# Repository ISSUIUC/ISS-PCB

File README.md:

# Welcome to the ISS-PCB repo! 🖥️⚙️⚡

# Repository Overview

* Boards: Contains all of the present boards the team is working on
    - Moved Board Archive to the [Archive](https://github.com/ISSUIUC/ISS-PCB-Archive) repo... check it out! 😁
* Docs: Contains various documents pertaining to PCB designs
* Libs: Contains various templates, symbols and footprints that we use when designing PCBs
* Scripts: Contains various codes used in PCB development
* Documentation & Tutorial Mark Down Files: 
    - README.md: Introduces the ISS-PCB Repo and pertinent information to become an amazing E-Hardware member
    - ISS-PCB-CONVENTIONS.md: Sets conventions to be followed when desiging for the ISS-PCB KiCad repo
    - HOW-TO.md: Presents brief and thorough lessons on important KiCad tools, documenation procedures, and design processes
    - GITHUB.md: An introduction to GitHub and how to use it for KiCad
    - CONTRIBUTING.md: Showcases how to setup KiCad and contribute proper work to E-Hardware. Additionally, introduces many conventions of ISS-PCB folder. 

When you commit changes to the repository, they will generally be found in the Boards folder. 

# E-Hardware PCB Documentation 

* You can find documentation about all of our PCBs in the [Spaceshot Members Box Folder](https://uofi.app.box.com/folder/273741222408). 
    - Alternatively, [Members] Spaceshot > Avionics > Development 

# How to contribute:
There are many ways to contribute to the PCBs that we build for the rocket and its accompanying systems. The timeline for building a PCB is usually as follows: 

* Formulate the requirements of the board
* Research different chips, understand their functionalities, and determine if we can use it for our purposes
* Build the board schematic using the datasheets of different chips 
* Route the board 
* Once the board is manufactured, solder all the components onto the board
* Debug the board 
* Document the board (this should be done throughout the process as well) 

Every part of constructing a PCB is hands-on, and there are lots of ways to get involved. 

To have your changes reflected on the board, it is important to commit your changes to the Github repository. To learn how to commit changes, check out the [Contributing Guide](/CONTRIBUTING.md).

# Useful Links:
Here are some links you may find useful as you are building PCBs: 

* [KiCad](https://www.kicad.org/) - software used for designing PCBs 

* [KiCad Library Conventions](https://klc.kicad.org/) - guidelines for creation of symbols, footprints, and 3D models in KiCad

* [DigiKey](https://www.digikey.com/) - used for looking up various electronic components

* [Mouser](https://www.mouser.com/) - used for looking up various electronic components

* [JLCPCB](https://jlcpcb.com) - the PCB manufacturer we primarily use

* [JLCPCB Design Rules](https://jlcpcb.com/capabilities/Capabilities) - the design constraints JLCPCB imposes

Thanks for reading, and good luck in building PCBs! 

*See a typo? Think we left some vital information out? Make a branch and edit this file!*

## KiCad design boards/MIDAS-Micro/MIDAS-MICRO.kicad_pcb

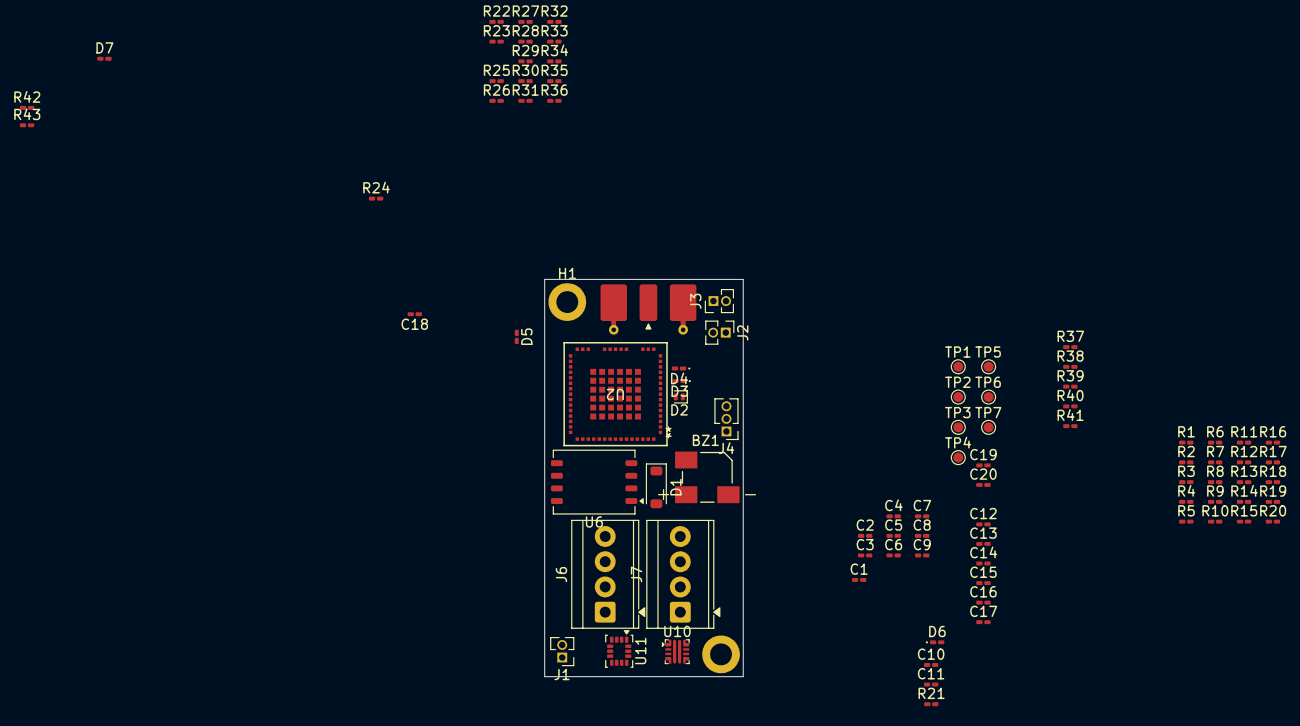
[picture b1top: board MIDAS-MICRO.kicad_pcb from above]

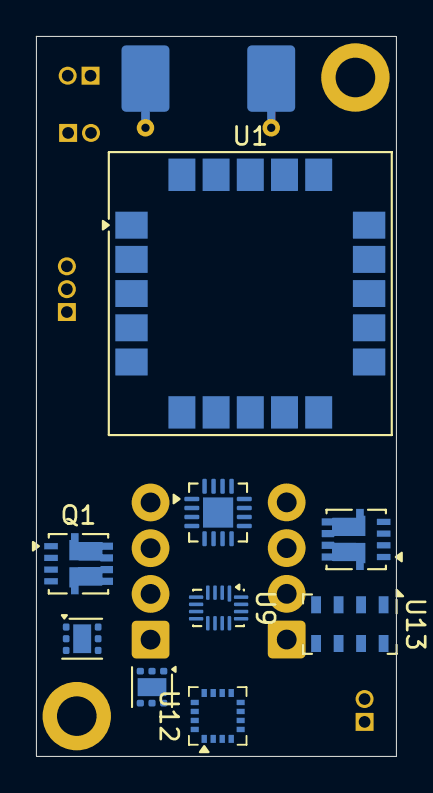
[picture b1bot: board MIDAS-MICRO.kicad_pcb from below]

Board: 2 copper layers, 20.0 x 40.0 mm, 100 parts (9 on the bottom side), 61 nets, no tracks yet.

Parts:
BZ1: Buzzer; XDCR_SMT-0540-T-9-R
C1, C2, C5, C6, C13, C15, C16, C17, C19, C20: 100nF; C_0201_0603Metric_Pad0.64x0.40mm_HandSolder
C3: 22uF; C_0201_0603Metric_Pad0.64x0.40mm_HandSolder
C4, C7, C8, C9, C10: 1uF; C_0201_0603Metric_Pad0.64x0.40mm_HandSolder
C11, C14: 4.7uF; C_0201_0603Metric_Pad0.64x0.40mm_HandSolder
C12: 4.7nF; C_0201_0603Metric_Pad0.64x0.40mm_HandSolder
C18: 10uF; C_0201_0603Metric_Pad0.64x0.40mm_HandSolder
D1: 1N4148W; D_SOD-123
D2: SDM05U40CSP; D_SOD-882
D3: RED LED; LED_0201_0603Metric_Pad0.64x0.40mm_HandSolder
D4: ORANGE LED; LED_0201_0603Metric_Pad0.64x0.40mm_HandSolder
D5: GREEN LED; L_0201_0603Metric_Pad0.64x0.40mm_HandSolder
D6: BLUE LED; LED_0201_0603Metric_Pad0.64x0.40mm_HandSolder
D7: RED LED; L_0201_0603Metric_Pad0.64x0.40mm_HandSolder
H1, H2: M2; MountingHole_2.2mm_M2_DIN965_Pad
J1, J2, J3: Conn_01x02; PinHeader_1x02_P1.27mm_Vertical
J4: Conn_01x03; PinHeader_1x03_P1.27mm_Vertical
J5: SMA; SMA_Molex_73251-2120_EdgeMount_Horizontal
J6, J7: Screw_Terminal_01x04; TerminalBlock_TE_282834-4_1x04_P2.54mm_Horizontal
Q1, Q2: Si7232DN; Vishay_PowerPAK_1212-8_Dual
R1, R25, R36, R40: 3.3k; R_0201_0603Metric_Pad0.64x0.40mm_HandSolder
R2, R29, R33, R37, R41: 1k; R_0201_0603Metric_Pad0.64x0.40mm_HandSolder
R3, R24, R28: 10k; R_0201_0603Metric_Pad0.64x0.40mm_HandSolder
R4: 560k; R_0201_0603Metric_Pad0.64x0.40mm_HandSolder
R5, R6, R7, R8, R9, R20, R27, R30, R35, R38, R42: 100k; R_0201_0603Metric_Pad0.64x0.40mm_HandSolder
R10, R11, R12, R13, R23: 470; R_0201_0603Metric_Pad0.64x0.40mm_HandSolder
R14, R15, R16, R18, R19: 50k; R_0201_0603Metric_Pad0.64x0.40mm_HandSolder
R17, R21: 4.7k; R_0201_0603Metric_Pad0.64x0.40mm_HandSolder
R22: 20k; R_0201_0603Metric_Pad0.64x0.40mm_HandSolder
R26, R34: 150k; R_0201_0603Metric_Pad0.64x0.40mm_HandSolder
R31, R39, R43: 18k; R_0201_0603Metric_Pad0.64x0.40mm_HandSolder
R32: 820; R_0201_0603Metric_Pad0.64x0.40mm_HandSolder
TP1, TP2, TP3, TP4, TP5, TP6, TP7: TestPoint_Small; TestPoint_Pad_D1.0mm
U1: SAM-M10Q; ublox_SAM-M8Q
U2: STM32WL5MOCH6STR; STM32WL5MOC
U5: ADS7138-Q1; WQFN-16-1EP_3x3mm_P0.5mm_EP1.68x1.68mm
U6: XTSD04G; LGA-8_8x6.2mm_P1.27mm
U7: TVS1800DRV; WSON-6-1EP_2x2mm_P0.65mm_EP1x1.6mm
U8: TPS746-Q1; WSON-6-1EP_2x2mm_P0.65mm_EP1x1.6mm
U9: TCAL9538; UQFN-16_1.8x2.6mm_P0.4mm
U10: TPS25947; VQFN-HR-RPW0010A
U11: LSM6DSV320X; LGA-14_3x2.5mm_P0.5mm_LayoutBorder3x4y
U12: MMC5983MA; LGA-16_3x3mm_P0.5mm
U13: MS5611-01BA; LGA-8_3x5mm_P1.25mm

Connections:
+3V3: C1.2, C2.2, C3.1, C5.1, C6.2, C7.1, C8.1, C11.1, C13.2, C15.1, C16.1, C17.1, C19.1, C20.1, D1.1 (K), J2.1, R14.2, R15.2, R16.2, R17.2, R18.2, R19.2, R21.2, R22.2, R23.1, R24.2, R28.2, R33.2, U1.2 (VCC_IO), U1.17 (VCC), U5.7 (AVDD), U5.10 (DVDD), U6.8 (VDD), U8.1 (OUT), U9.14 (VCC), U11.5 (VDDIO), U11.8 (VDD), U12.2 (VDD), U12.13 (VDDIO), U13.1 (VDD)
/ANT: J5.1 (In), U2.17 (ANT)
/BUZZER: R1.1, R2.1
/EXP_INT: R28.1, U9.11 (INT)
/EXP_RESET: R24.1, TP1.1 (1_1), U9.1 (~RESET)
/FLASH_CMD: R19.1, TP5.1 (1_1)
/FLASH_DAT0: R14.1, TP7.1 (1_1)
/I2C_SCL: R21.1, U1.12 (SCL), U2.42 (PA12), U5.13 (SCL), U9.12 (SCL)
/I2C_SDA: R17.1, U1.9 (SDA), U2.40 (PA11), U5.14 (SDA), U9.13 (SDA)
/JTCK/SWCLK: J4.2, U2.46 (PA14)
/JTDO: J4.3, U2.56 (PB3)
/JTMS/SWDIO: J4.1, U2.41 (PA13)
/LED_BLUE: R13.1, U2.6 (PA1)
/LED_GREEN: R12.1, U2.9 (PA2)
/LED_ORANGE: R11.1, U2.8 (PA3)
/LED_RED: R10.1, U2.12 (PA4)
/LSM_CS: TP4.1 (1_1), U2.31 (PA9), U11.12 (CS)
/MAG_CS: TP2.1 (1_1), U2.14 (PA8), U12.4 (CS)
/MS5611_CS: TP3.1 (1_1), U2.39 (PA10), U13.4 (CSB), U13.5 (CSB)
/NRST: C9.1, R22.1, U2.1 (NRST)
/PYRO_A: J6.2, Q2.6 (D1), R30.2
/PYRO_B: J6.4, Q2.5 (D2), R38.2
/PYRO_C: J7.3, Q1.5 (D2), R42.2
/PYRO_SENSE: R4.2, R5.1, U5.1 (ANI2/GPIO2)
/Pyro/FIRE_A: R25.1, R29.1, U9.2 (P0)
/Pyro/FIRE_B: R36.1, R37.1, U9.3 (P1)
/Pyro/FIRE_C: R40.1, R41.1, U9.10 (P7)
/Pyro/PGTH: R34.2, R35.1, U10.4 (PGTH/NFLT)
/Pyro/PYRO_EN: R26.2, R27.1, U9.5 (P3), U10.1 (EN/UVLO)
/Pyro/PYRO_PG: R33.1, U9.7 (P4), U10.3 (PG/AUXOFF)
/SENSE_A: R30.1, R31.2, U5.15 (AIN0/GPIO0)
/SENSE_B: R38.1, R39.2, U5.16 (AIN1/GPIO1)
/SENSE_C: R42.1, R43.2, U5.3 (AIN4/GPIO4)
/SPI_MISO: U2.50 (PA6), U11.1 (SDO/TA0), U12.5 (SDO), U13.6 (SDO)
/SPI_MOSI: U2.10 (PA7), U11.14 (SDA), U12.16 (SDI), U13.7 (SDI/SDA)
/SPI_SCK: U2.13 (PA5), U11.13 (SCL), U12.1 (SCK), U13.8 (SCLK)
/VBAT: C10.1, J7.2, U7.4 (IN), U7.5 (IN), U7.6 (IN), U8.4 (EN), U8.6 (IN)
/VBAT_PYRO: D2.2 (A), J1.1, R26.1, U10.5 (IN)
/VBAT_SENSE: R6.2, R7.1, U5.6 (AIN7/GPIO7)
/VCAP_SENSE: R8.2, R9.1, U5.5 (AIN6/GPIO6)
/V_PYRO: C14.1, J6.1, J6.3, J7.4, R34.1, U10.6 (OUT)
GND: C1.1, C2.1, C3.2, C4.2, C5.2, C6.1, C7.2, C8.2, C9.2, C10.2, C11.2, C12.2, C13.1, C14.2, C15.2, C16.2, C17.2, C18.2, C19.2, C20.2, D3.1 (K), D4.1 (K), D5.1 (K), D6.1 (K), D7.1 (K), J1.2, J2.2, J5.2 (Ext), J7.1, Q1.1 (S1), Q1.3 (S2), Q2.1 (S1), Q2.3 (S2), R1.2, R3.1, R5.2, R7.2, R9.2, R25.2, R27.2, R31.1, R32.2, R35.2, R36.2, R39.1, R40.2, R43.1, U1.1 (GND), U1.4 (GND), U1.5 (GND), U1.6 (GND), U1.10 (GND), U1.11 (GND), U1.15 (GND), U1.16 (GND), U1.20 (GND), U2.24 (BIAS_LP), U5.9 (GND), U5.17 (EPAD), U6.4 (VSS), U7.1 (GND), U7.2 (GND), U7.3 (GND), U7.7 (GND), U8.3 (GND), U8.7 (EP), U9.6 (GND), U9.15 (A0), U9.16 (A1), U10.8 (GND), U11.2 (SDx), U11.3 (SCx), U11.6 (GND), U11.7 (GND), U12.9 (GND), U12.11 (GND), U13.2 (PS), U13.3 (GND)
unnamed: D1.2 (A), Q1.6 (D1)
unnamed: D2.1 (K), R4.1
unnamed: D3.2 (A), R10.2
unnamed: D4.2 (A), R11.2
unnamed: D5.2 (A), R12.2
unnamed: D6.2 (A), R13.2
unnamed: D7.2 (A), R23.2
unnamed: Q1.2 (G1), R2.2
unnamed: Q1.4 (G2), R41.2
unnamed: Q2.2 (G1), R29.2
unnamed: Q2.4 (G2), R37.2
unnamed: R3.2, U2.15 (PH3-BOOT0)
unnamed: R20.1, U5.11 (ADDR)
unnamed: C4.1, R20.2, U5.8 (DECAP)
unnamed: R32.1, U10.9 (ILM)
unnamed: C12.1, U10.10 (ITIMER)
unnamed: C18.1, U12.10 (CAP)
VSS: U2.19 (VSS), U2.20 (VSS), U2.21 (VSS), U2.22 (VSS), U2.23 (VSS), U2.57 (VSS), U2.58 (VSS), U2.59 (VSS), U2.60 (VSS), U2.61 (VSS), U2.62 (VSS), U2.63 (VSS), U2.64 (VSS), U2.65 (VSS), U2.66 (VSS), U2.67 (VSS), U2.68 (VSS), U2.69 (VSS), U2.70 (VSS), U2.71 (VSS), U2.72 (VSS), U2.73 (VSS), U2.74 (VSS), U2.75 (VSS), U2.76 (VSS), U2.77 (VSS), U2.78 (VSS), U2.79 (VSS), U2.80 (VSS), U2.81 (VSS), U2.82 (VSS), U2.83 (VSS), U2.84 (VSS), U2.85 (VSS), U2.86 (VSS), U2.87 (VSS), U2.88 (VSS), U2.89 (VSS), U2.90 (VSS), U2.91 (VSS), U2.92 (VSS)
VSSRF: U2.16 (VSSRF), U2.18 (VSSRF)

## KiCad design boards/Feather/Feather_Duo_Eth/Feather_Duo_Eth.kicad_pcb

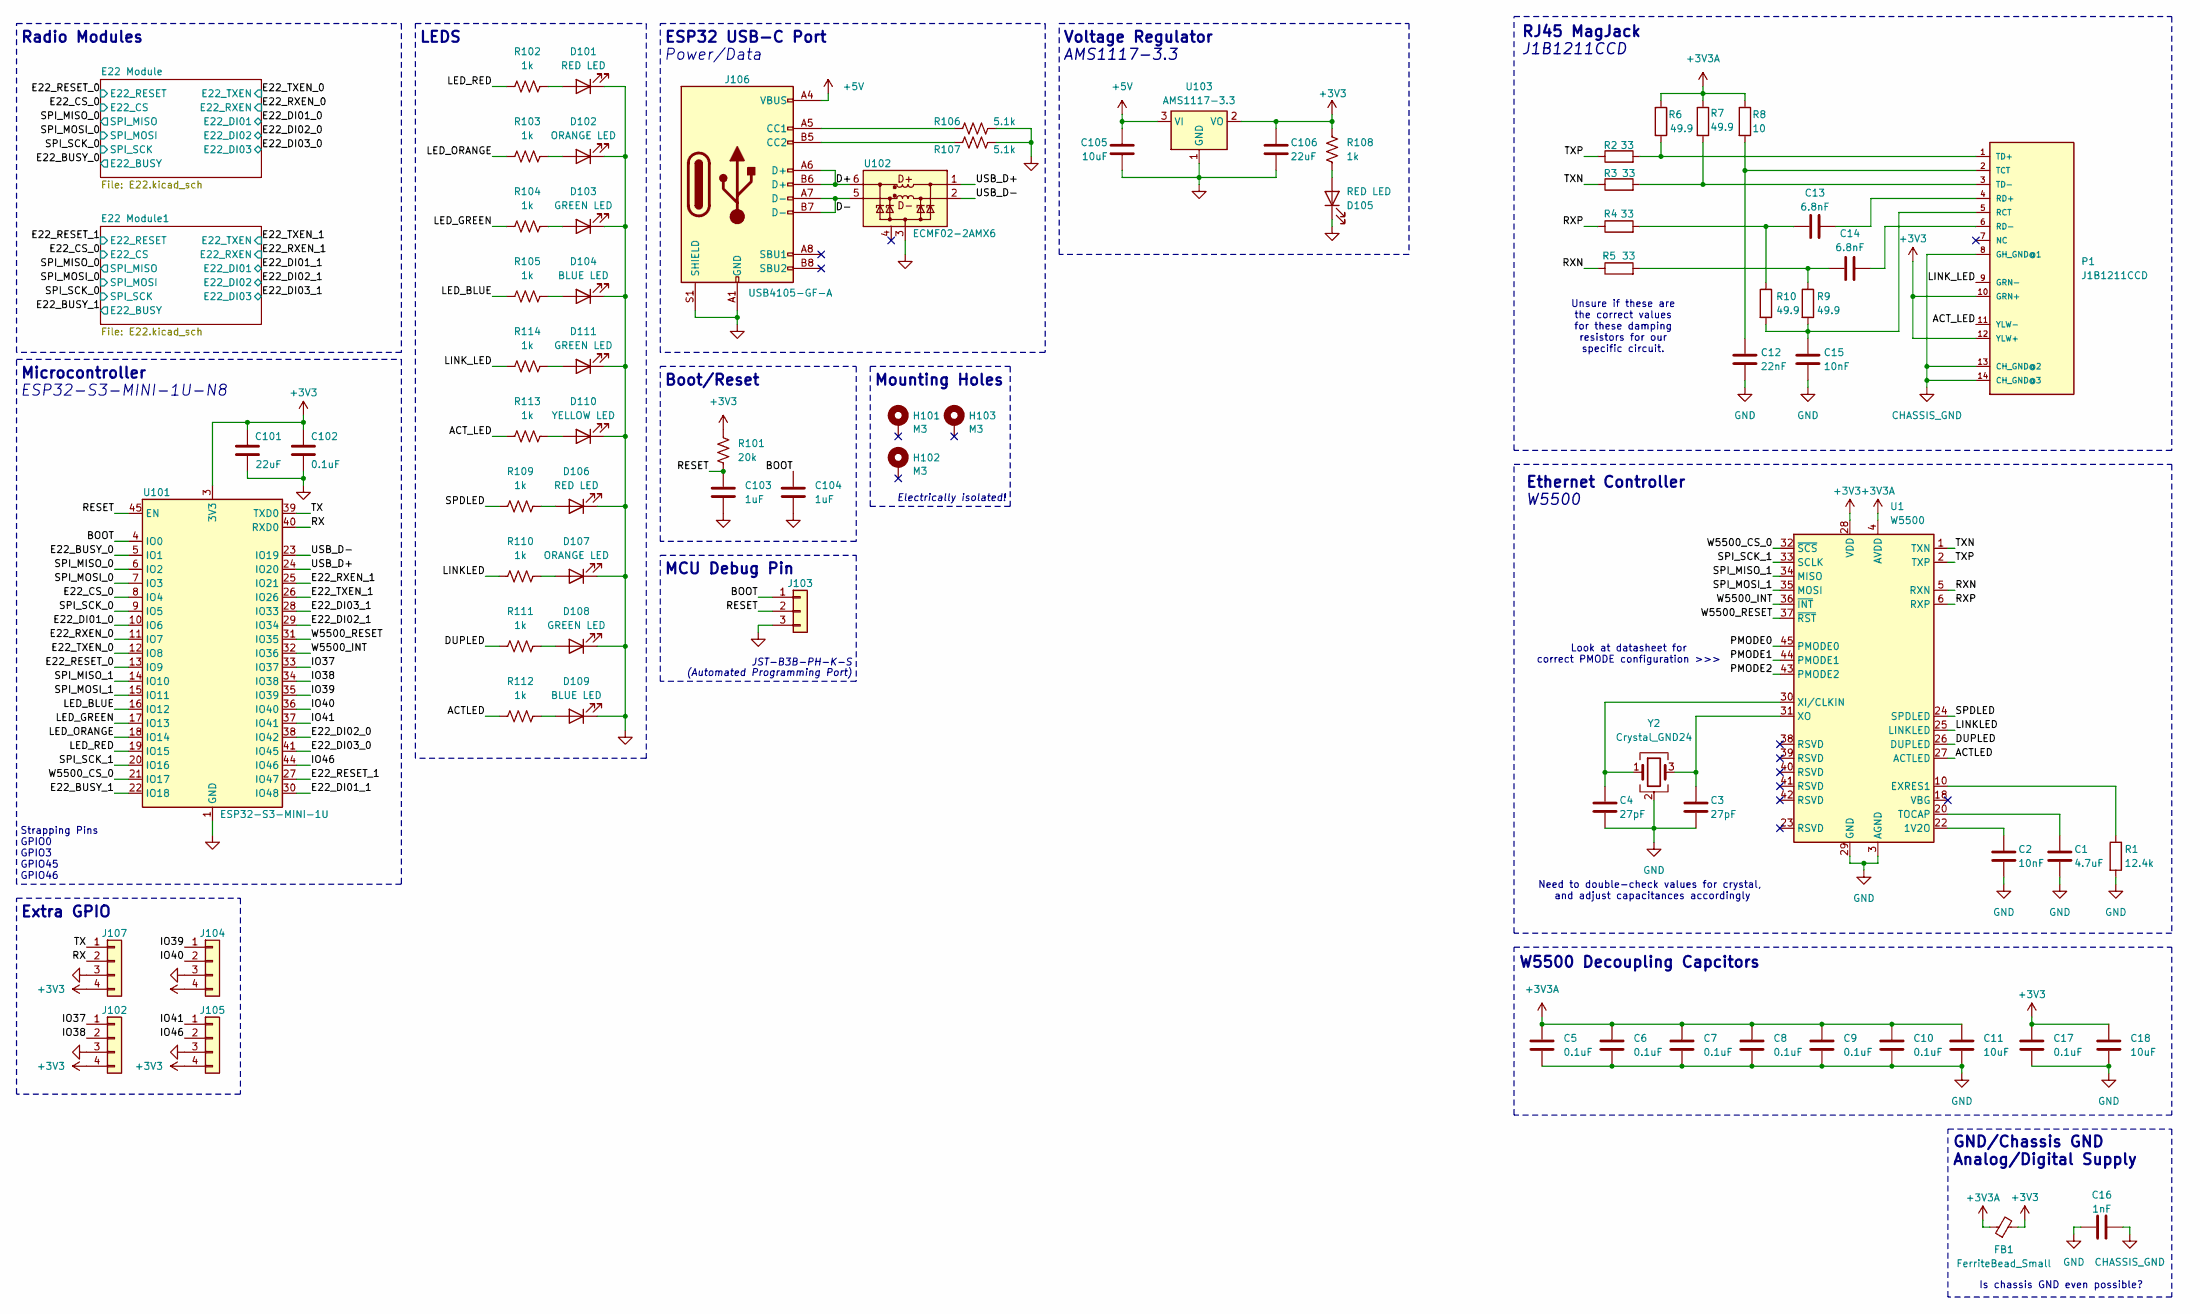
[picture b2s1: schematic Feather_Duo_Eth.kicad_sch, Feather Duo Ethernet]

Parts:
C1: 4.7uF; C_0603_1608Metric
C2, C15: 10nF; C_0603_1608Metric
C3, C4: 27pF; C_0603_1608Metric
C5, C6, C7, C8, C9, C10, C17, C102: 0.1uF; C_0603_1608Metric
C11, C18, C105: 10uF; C_0603_1608Metric
C12: 22nF; C_0603_1608Metric
C13, C14: 6.8nF; C_0603_1608Metric
C16: 1nF; C_0603_1608Metric
C101, C106: 22uF; C_0603_1608Metric
C103, C104: 1uF; C_0603_1608Metric
D101, D105, D106: RED LED; LED_0603_1608Metric
D102, D107: ORANGE LED; LED_0603_1608Metric
D103, D108, D111: GREEN LED; LED_0603_1608Metric
D104, D109: BLUE LED; LED_0603_1608Metric
D110: YELLOW LED; LED_0603_1608Metric
FB1: FerriteBead_Small; L_0805_2012Metric
H101, H102, H103: M3; MountingHole_3.2mm_M3_Pad_Via
J102, J104, J105, J107: Conn_01x04; PinHeader_1x04_P2.54mm_Vertical
J103: Conn_01x03; JST_PH_B3B-PH-K_1x03_P2.00mm_Vertical
J106: USB4105-GF-A; USB_C_Receptacle_GCT_USB4105-xx-A_16P_TopMnt_Horizontal
P1: J1B1211CCD
R1: 12.4k; R_0603_1608Metric
R2, R3, R4, R5: 33; R_0603_1608Metric
R6, R7, R9, R10: 49.9; R_0603_1608Metric
R8: 10; R_0603_1608Metric
R101: 20k; R_0603_1608Metric
R102, R103, R104, R105, R108, R109, R110, R111, R112, R113, R114: 1k; R_0603_1608Metric
R106, R107: 5.1k; R_0603_1608Metric
U1: W5500; LQFP-48_7x7mm_P0.5mm
U101: ESP32-S3-MINI-1U; ESP32-S2-MINI-1U
U102: ECMF02-2AMX6; ST_UQFN-6L_1.5x1.7mm_P0.5mm
U103: AMS1117-3.3; SOT-223-3_TabPin2
Y2: Crystal_GND24; Crystal_SMD_3225-4Pin_3.2x2.5mm

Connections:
+3V3: C17.1, C18.1, C101.2, C102.2, C106.1, FB1.2, J102.4, J104.4, J105.4, J107.4, P1.10 (GRN+), P1.12 (YLW+), R101.1, R108.1, U1.28 (VDD), U101.3 (3V3), U103.2 (VO); also elsewhere on the board
+3V3A: C5.1, C6.1, C7.1, C8.1, C9.1, C10.1, C11.1, FB1.1, R6.1, R7.1, R8.1, U1.4 (AVDD), U1.8 (AVDD), U1.11 (AVDD), U1.15 (AVDD), U1.17 (AVDD), U1.21 (AVDD)
+5V: C105.1, J106.A4 (VBUS), J106.A9 (VBUS), J106.B4 (VBUS), J106.B9 (VBUS), U103.3 (VI)
/ACTLED: R112.1, U1.27 (ACTLED)
/ACT_LED: P1.11 (YLW-), R113.1
/BOOT: C104.1, J103.1, U101.4 (IO0)
/D+: J106.A6 (D+), J106.B6 (D+), U102.6 (D+_out)
/D-: J106.A7 (D-), J106.B7 (D-), U102.5 (D-_out)
/DUPLED: R111.1, U1.26 (DUPLED)
/E22_BUSY_0: U101.5 (IO1); also elsewhere on the board
/E22_BUSY_1: U101.22 (IO18); also elsewhere on the board
/E22_CS_0: U101.8 (IO4); also elsewhere on the board
/E22_DI01_0: U101.10 (IO6); also elsewhere on the board
/E22_DI01_1: U101.30 (IO48); also elsewhere on the board
/E22_DI02_0: U101.38 (IO42); also elsewhere on the board
/E22_DI02_1: U101.29 (IO34); also elsewhere on the board
/E22_DI03_0: U101.41 (IO45); also elsewhere on the board
/E22_DI03_1: U101.28 (IO33); also elsewhere on the board
/E22_RESET_0: U101.13 (IO9); also elsewhere on the board
/E22_RESET_1: U101.27 (IO47); also elsewhere on the board
/E22_RXEN_0: U101.11 (IO7); also elsewhere on the board
/E22_RXEN_1: U101.25 (IO21); also elsewhere on the board
/E22_TXEN_0: U101.12 (IO8); also elsewhere on the board
/E22_TXEN_1: U101.26 (IO26); also elsewhere on the board
/IO37: J102.1, U101.33 (IO37)
/IO38: J102.2, U101.34 (IO38)
/IO39: J104.1, U101.35 (IO39)
/IO40: J104.2, U101.36 (IO40)
/IO41: J105.1, U101.37 (IO41)
/IO46: J105.2, U101.44 (IO46)
/LED_BLUE: R105.1, U101.16 (IO12)
/LED_GREEN: R104.1, U101.17 (IO13)
/LED_ORANGE: R103.1, U101.18 (IO14)
/LED_RED: R102.1, U101.19 (IO15)
/LINKLED: R110.1, U1.25 (LINKLED)
/LINK_LED: P1.9 (GRN-), R114.1
/PMODE0: U1.45 (PMODE0)
/PMODE1: U1.44 (PMODE1)
/PMODE2: U1.43 (PMODE2)
/RESET: C103.1, J103.2, R101.2, U101.45 (EN)
/RX: J107.2, U101.40 (RXD0)
/RXN: R5.1, U1.5 (RXN)
/RXP: R4.1, U1.6 (RXP)
/SPDLED: R109.1, U1.24 (SPDLED)
/SPI_MISO_0: U101.6 (IO2); also elsewhere on the board
/SPI_MISO_1: U1.34 (MISO), U101.14 (IO10)
/SPI_MOSI_0: U101.7 (IO3); also elsewhere on the board
/SPI_MOSI_1: U1.35 (MOSI), U101.15 (IO11)
/SPI_SCK_0: U101.9 (IO5); also elsewhere on the board
/SPI_SCK_1: U1.33 (SCLK), U101.20 (IO16)
/TX: J107.1, U101.39 (TXD0)
/TXN: R3.1, U1.1 (TXN)
/TXP: R2.1, U1.2 (TXP)
/USB_D+: U101.24 (IO20), U102.1 (D+_in)
/USB_D-: U101.23 (IO19), U102.2 (D-_in)
/W5500_CS_0: U1.32 (~SCS), U101.21 (IO17)
/W5500_INT: U1.36 (~INT), U101.32 (IO36)
/W5500_RESET: U1.37 (~RST), U101.31 (IO35)
CHASSIS_GND: C16.2, P1.8 (GH_GND@1), P1.13 (CH_GND@2), P1.14 (CH_GND@3)
GND: C1.2, C2.2, C3.2, C4.2, C5.2, C6.2, C7.2, C8.2, C9.2, C10.2, C11.2, C12.2, C15.2, C16.1, C17.2, C18.2, C101.1, C102.1, C103.2, C104.2, C105.2, C106.2, D101.1 (K), D102.1 (K), D103.1 (K), D104.1 (K), D105.1 (K), D106.1 (K), D107.1 (K), D108.1 (K), D109.1 (K), D110.1 (K), D111.1 (K), J102.3, J103.3, J104.3, J105.3, J106.A1 (GND), J106.A12 (GND), J106.B1 (GND), J106.B12 (GND), J106.S1 (SHIELD), J107.3, R1.2, R106.2, R107.2, U1.3 (AGND), U1.9 (AGND), U1.14 (AGND), U1.16 (AGND), U1.19 (AGND), U1.29 (GND), U1.48 (AGND), U101.1 (GND), U101.2 (GND), U101.42 (GND), U101.43 (GND), U101.46 (GND), U101.47 (GND), U101.48 (GND), U101.49 (GND), U101.50 (GND), U101.51 (GND), U101.52 (GND), U101.53 (GND), U101.54 (GND), U101.55 (GND), U101.56 (GND), U101.57 (GND), U101.58 (GND), U101.59 (GND), U101.60 (GND), U101.61 (GND), U101.62 (GND), U101.63 (GND), U101.64 (GND), U101.65 (GND), U102.3 (GND), U103.1 (GND), Y2.2 (G), Y2.4 (G); also elsewhere on the board
unnamed: C13.1, R4.2, R10.1
unnamed: C14.1, R5.2, R9.1
unnamed: D101.2 (A), R102.2
unnamed: D102.2 (A), R103.2
unnamed: D103.2 (A), R104.2
unnamed: D104.2 (A), R105.2
unnamed: D105.2 (A), R108.2
unnamed: D106.2 (A), R109.2
unnamed: D107.2 (A), R110.2
unnamed: D108.2 (A), R111.2
unnamed: D109.2 (A), R112.2
unnamed: D110.2 (A), R113.2
unnamed: D111.2 (A), R114.2
unnamed: J106.A5 (CC1), R106.1
unnamed: J106.B5 (CC2), R107.1
unnamed: C15.1, P1.5 (RCT), R9.2, R10.2
unnamed: C13.2, P1.4 (RD+)
unnamed: C14.2, P1.6 (RD-)
unnamed: C12.1, P1.2 (TCT), R8.2
unnamed: P1.1 (TD+), R2.2, R6.2
unnamed: P1.3 (TD-), R3.2, R7.2
unnamed: C2.1, U1.22 (1V2O)
unnamed: R1.1, U1.10 (EXRES1)
unnamed: C1.1, U1.20 (TOCAP)
unnamed: C4.1, U1.30 (XI/CLKIN), Y2.1
unnamed: C3.1, U1.31 (XO), Y2.3

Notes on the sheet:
Microcontroller
Look at datasheet for correct PMODE configuration >>>
MCU Debug Pin
Electrically isolated!
LEDS
Unsure if these are the correct values for these damping resistors for our specific circuit.
Voltage Regulator
Need to double-check values for crystal, and adjust capacitances accordingly
AMS1117-3.3
W5500
JST-B3B-PH-K-S
Ethernet Controller
Radio Modules
Is chassis GND even possible?
W5500 Decoupling Capcitors
J1B1211CCD
ESP32-S3-MINI-1U-N8
Extra GPIO
RJ45 MagJack
GND/Chassis GND Analog/Digital Supply
ESP32 USB-C Port
Strapping Pins GPIO0 GPIO3 GPIO45 GPIO46
Power/Data
(Automated Programming Port)
Mounting Holes
Boot/Reset

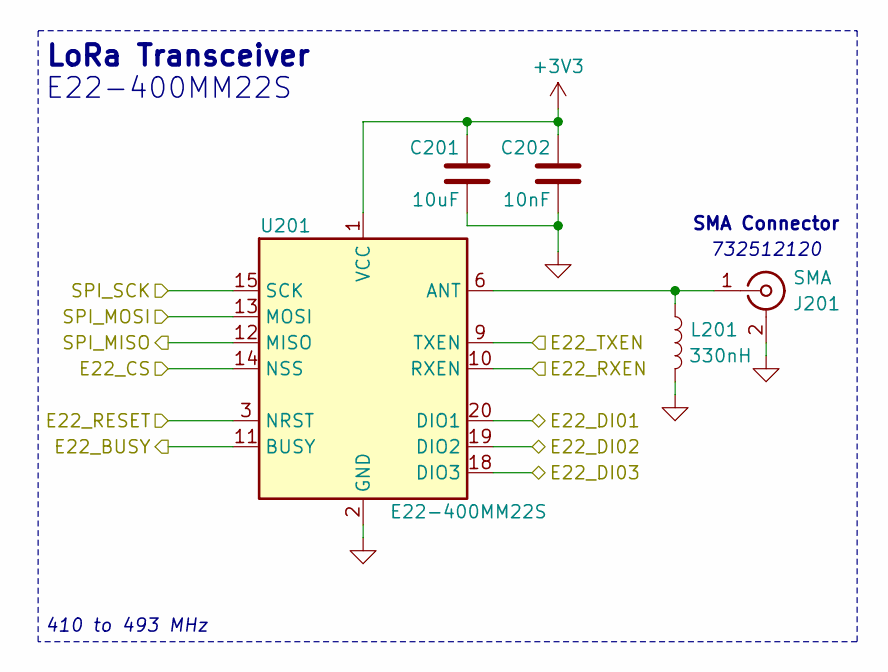
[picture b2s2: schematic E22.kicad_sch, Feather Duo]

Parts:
C201: 10uF; C_0603_1608Metric
C202: 10nF; C_0603_1608Metric
J201: SMA; SMA_Molex_73251-2120_EdgeMount_Horizontal
L201: 330nH; L_0603_1608Metric
U201: E22-400MM22S

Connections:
+3V3: C201.1, C202.1, U201.1 (VCC); also elsewhere on the board
/E22_BUSY_0: U201.11 (BUSY); also elsewhere on the board
/E22_CS_0: U201.14 (NSS); also elsewhere on the board
/E22_DI01_0: U201.20 (DIO1); also elsewhere on the board
/E22_DI02_0: U201.19 (DIO2); also elsewhere on the board
/E22_DI03_0: U201.18 (DIO3); also elsewhere on the board
/E22_RESET_0: U201.3 (NRST); also elsewhere on the board
/E22_RXEN_0: U201.10 (RXEN); also elsewhere on the board
/E22_TXEN_0: U201.9 (TXEN); also elsewhere on the board
/SPI_MISO_0: U201.12 (MISO); also elsewhere on the board
/SPI_MOSI_0: U201.13 (MOSI); also elsewhere on the board
/SPI_SCK_0: U201.15 (SCK); also elsewhere on the board
GND: C201.2, C202.2, J201.2 (Ext), L201.2, U201.2 (GND), U201.7 (GND), U201.16 (GND); also elsewhere on the board
unnamed: J201.1 (In), L201.1, U201.6 (ANT)

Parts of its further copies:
C301: 10uF; C_0603_1608Metric
C302: 10nF; C_0603_1608Metric
J301: SMA; SMA_Molex_73251-2120_EdgeMount_Horizontal
L301: 330nH; L_0603_1608Metric
U301: E22-400MM22S

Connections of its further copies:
+3V3: C301.1, C302.1, U301.1 (VCC); also elsewhere on the board
/E22_BUSY_1: U301.11 (BUSY); also elsewhere on the board
/E22_CS_0: U301.14 (NSS); also elsewhere on the board
/E22_DI01_1: U301.20 (DIO1); also elsewhere on the board
/E22_DI02_1: U301.19 (DIO2); also elsewhere on the board
/E22_DI03_1: U301.18 (DIO3); also elsewhere on the board
/E22_RESET_1: U301.3 (NRST); also elsewhere on the board
/E22_RXEN_1: U301.10 (RXEN); also elsewhere on the board
/E22_TXEN_1: U301.9 (TXEN); also elsewhere on the board
/SPI_MISO_0: U301.12 (MISO); also elsewhere on the board
/SPI_MOSI_0: U301.13 (MOSI); also elsewhere on the board
/SPI_SCK_0: U301.15 (SCK); also elsewhere on the board
GND: C301.2, C302.2, J301.2 (Ext), L301.2, U301.2 (GND), U301.7 (GND), U301.16 (GND); also elsewhere on the board
unnamed: J301.1 (In), L301.1, U301.6 (ANT)

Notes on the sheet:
SMA Connector
LoRa Transceiver
E22-400MM22S
410 to 493 MHz
732512120

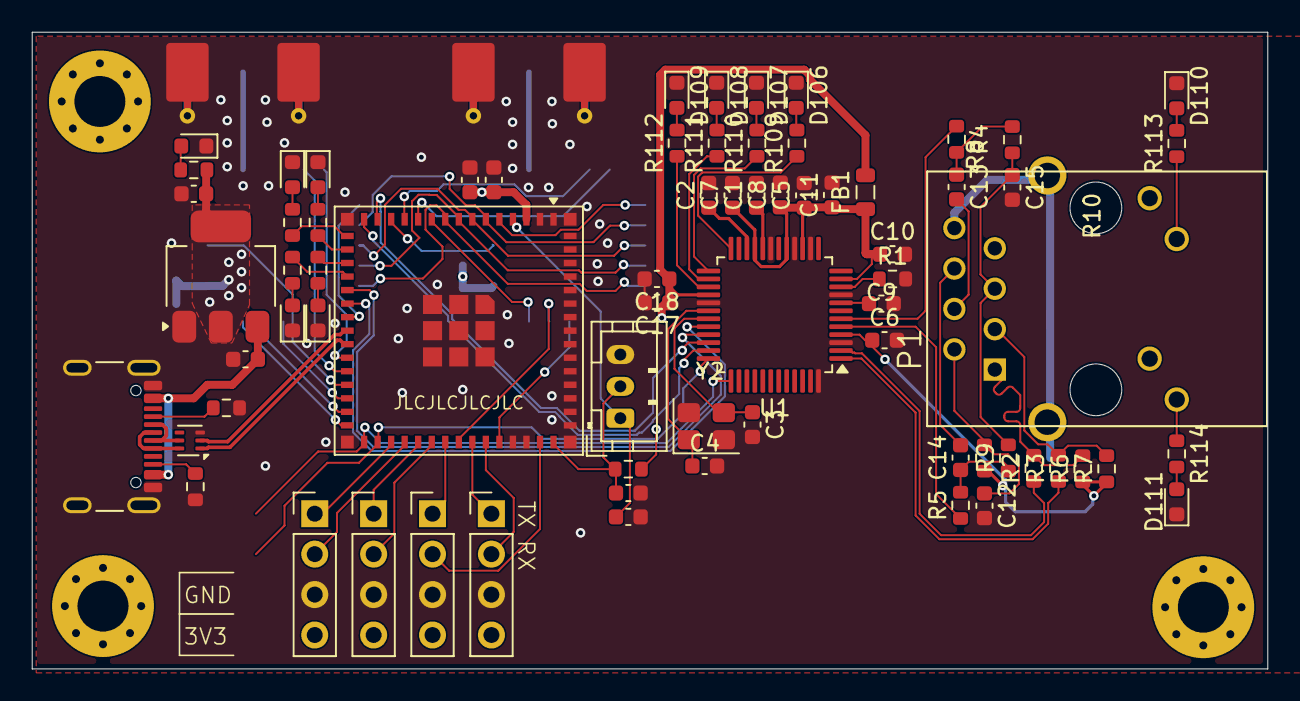
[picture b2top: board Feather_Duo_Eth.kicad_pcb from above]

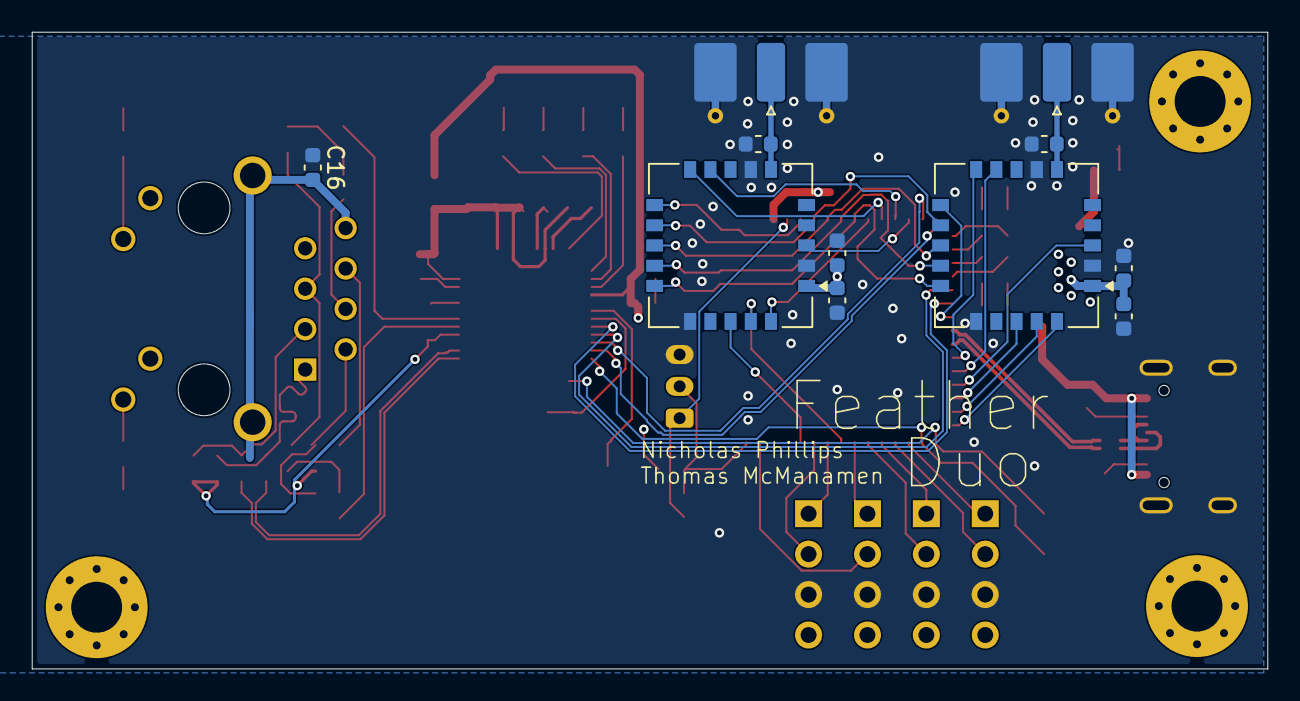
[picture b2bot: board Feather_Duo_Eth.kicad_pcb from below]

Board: 4 copper layers, 77.6 x 40.0 mm, 85 parts (11 on the bottom side), 85 nets.

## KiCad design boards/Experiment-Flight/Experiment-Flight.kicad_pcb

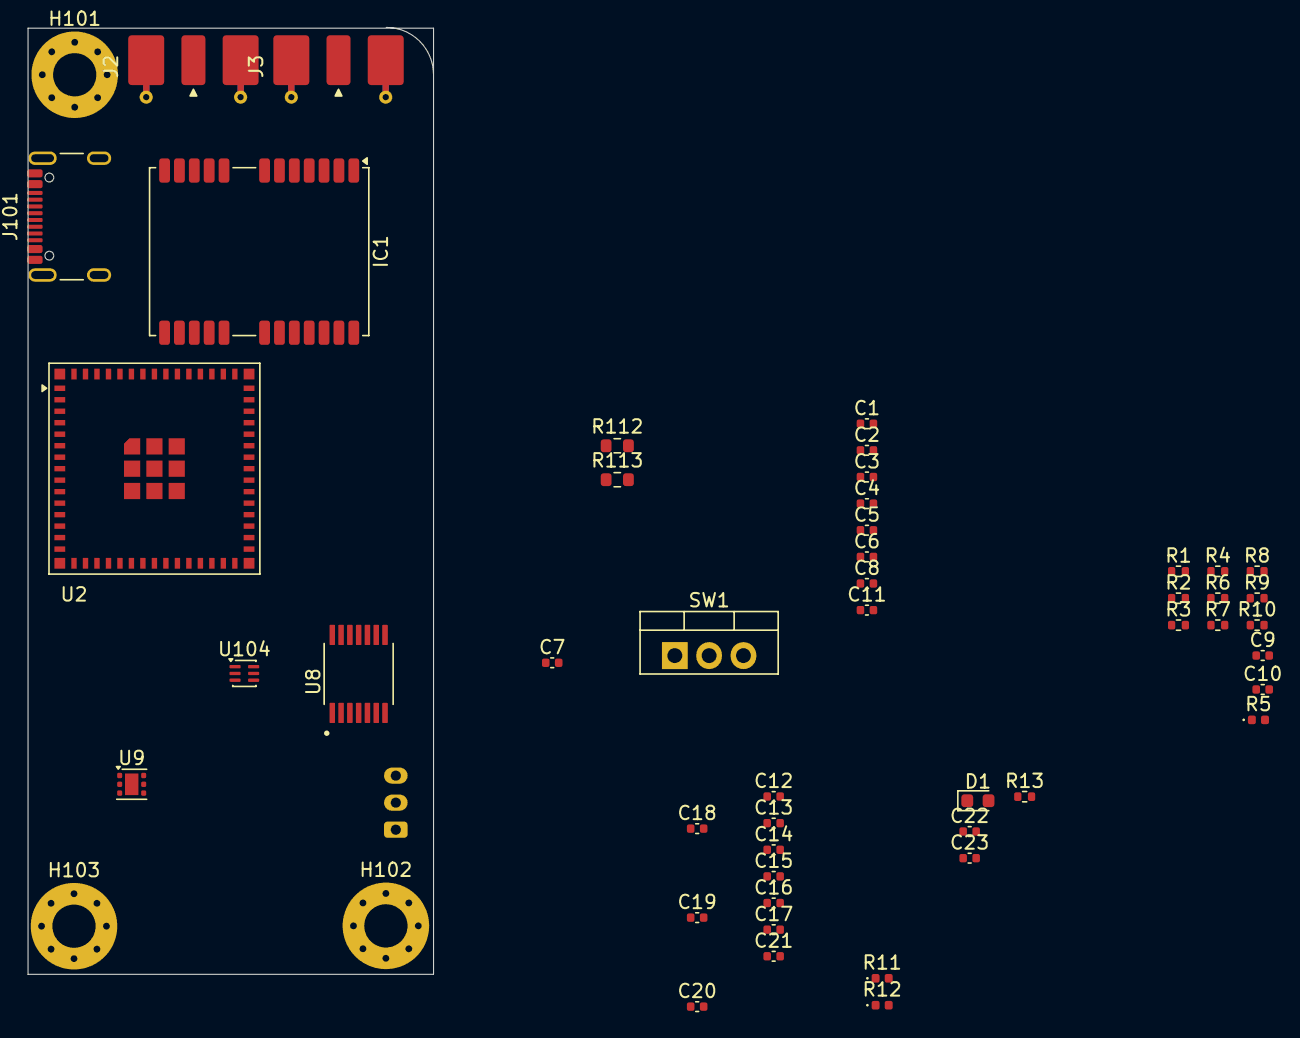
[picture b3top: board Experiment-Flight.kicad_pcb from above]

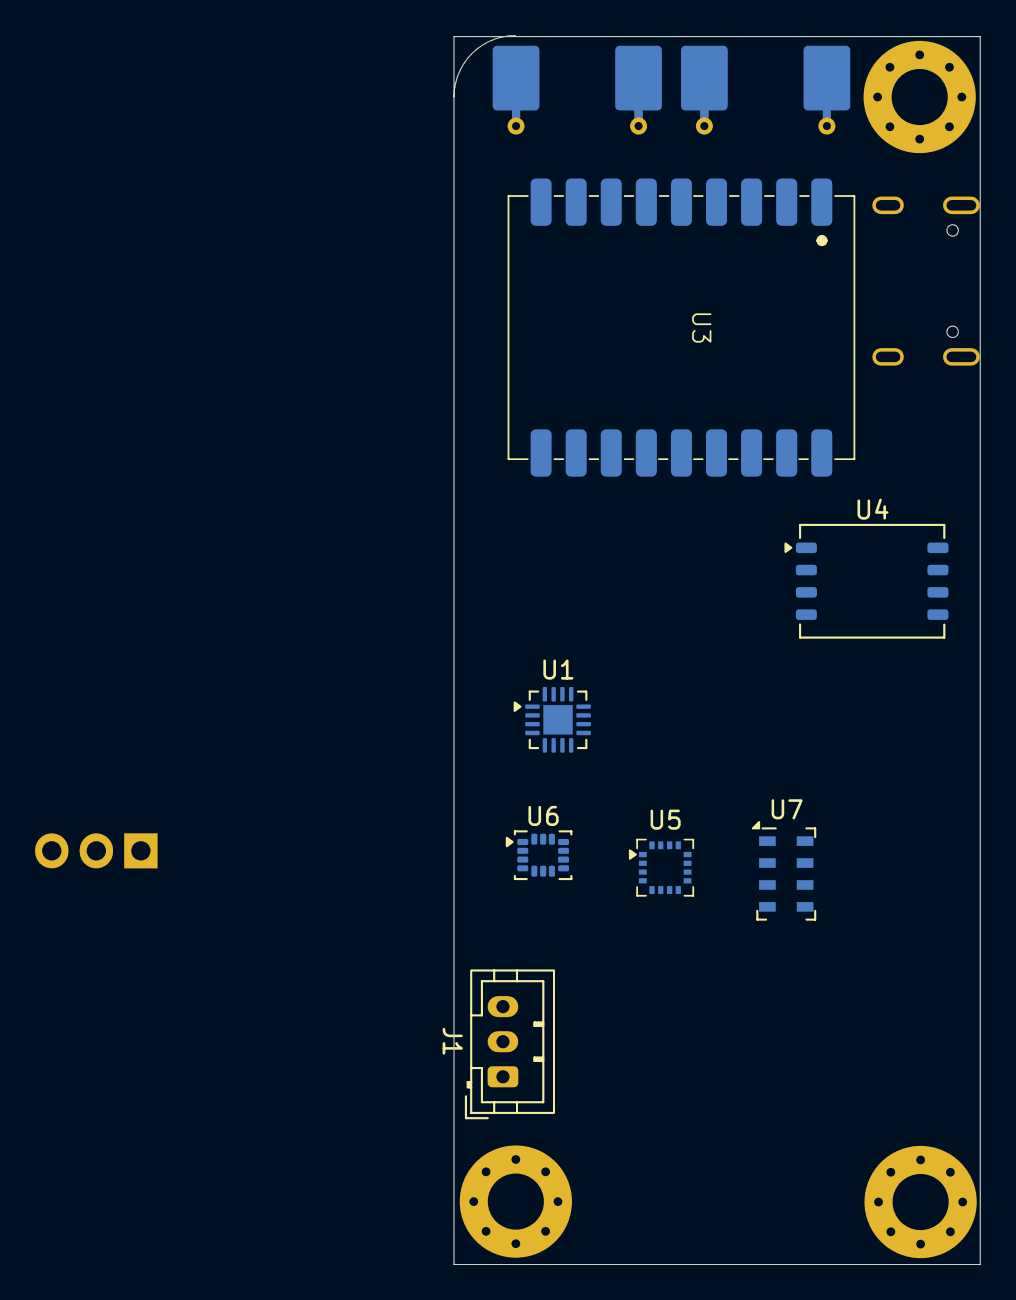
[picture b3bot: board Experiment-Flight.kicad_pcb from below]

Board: 2 copper layers, 30.0 x 70.0 mm, 58 parts (7 on the bottom side), 30 nets, no tracks yet.

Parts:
C1, C2, C3, C5, C8, C9, C22: 1uF; C_0402_1005Metric
C4, C6, C19, C21: 0.1uF; C_0402_1005Metric
C7: 22uF; C_0402_1005Metric
C10, C11, C12, C14, C15, C16, C17: 100nF; C_0402_1005Metric
C13: 10uF; C_0402_1005Metric
C18, C20: 0.01uF; C_0402_1005Metric
C23: 4.7uF; C_0402_1005Metric
D1: RED LED; LED_0603_1608Metric
H101, H102, H103: MountingHole; MountingHole_3.2mm_M3_Pad_Via
IC1: NEO-F10N-00B; ublox_NEO
J1: Conn_01x03; JST_PH_B3B-PH-K_1x03_P2.00mm_Vertical
J2, J3: SMA; SMA_Molex_73251-2120_EdgeMount_Horizontal
J101: USB4105-GF-A; USB_C_Receptacle_GCT_USB4105-xx-A_16P_TopMnt_Horizontal
R1: 100k; R_0402_1005Metric
R2: 10k; R_0402_1005Metric
R3: R_US; R_0402_1005Metric
R4: 20k; R_0402_1005Metric
R5, R11, R12: R_US; LED_0402_1005Metric
R6, R7, R8, R9, R10: 50k; R_0402_1005Metric
R13: 470; R_0402_1005Metric
R112, R113: 5.1k; R_0603_1608Metric
SW1: TO-220-3_Vertical
U1: ADS7138-Q1; WQFN-16-1EP_3x3mm_P0.5mm_EP1.68x1.68mm
U2: ESP32-S3-WROOM-1U; ESP32-S2-MINI-1U
U3: LR2021
U4: ZDSD64GLGEAG-R; LGA-8_8x6.2mm_P1.27mm
U5: MMC5983MA; LGA-16_3x3mm_P0.5mm
U6: LSM6DSV320X; LGA-14_3x2.5mm_P0.5mm_LayoutBorder3x4y
U7: MS5611-01BA; LGA-8_3x5mm_P1.25mm
U8: MAX31856MUD_T; MAX31856
U9: TPS746-Q1; WSON-6-1EP_2x2mm_P0.65mm_EP1x1.6mm
U104: ECMF02-2AMX6; ST_UQFN-6L_1.5x1.7mm_P0.5mm

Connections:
+3V3: C2.1, C3.1, C9.1, C10.1, C11.2, C12.1, C14.1, C15.1, C16.1, C17.1, C21.1, C23.1, IC1.22 (V_BCKP), IC1.23 (VCC), R4.2, R5.1, R6.2, R7.2, R8.2, R9.2, R10.2, R13.1, U1.7 (AVDD), U1.10 (DVDD), U3.1 (VCC), U4.8 (VDD), U5.2 (VDD), U5.13 (VDDIO), U6.5 (VDDIO), U6.8 (VDD), U7.1 (VDD), U8.5 (AVDD), U8.8 (DVDD), U9.1 (OUT)
/3.3V: C6.1, C7.1, R2.1, U2.2 (3V3)
/D+: J101.A6 (D+), J101.B6 (D+), U104.6 (D+_out)
/D-: J101.A7 (D-), J101.B7 (D-), U104.5 (D-_out)
/EN: C5.2, R2.2, R3.2, U2.3 (EN)
/FLASH_CMD: R10.1, U4.5 (CMD)
/FLASH_DAT0: R6.1, U4.6 (DAT0)
/FLASH_DAT1: R7.1, U4.7 (DAT1)
/FLASH_DAT2: R8.1, U4.1 (DAT2)
/FLASH_DAT3: R9.1, U4.2 (DAT3)
/LR2021_ANT: J2.1 (In), J3.1 (In), U3.9 (ANT)
/N_GNSS_RESET: IC1.8 (RESET_N), R5.2
/Power/SYS_POWER: C22.1, U9.4 (EN), U9.6 (IN)
/RESET_SW: C8.1, J1.2, R4.1
/Sensors/MS5611_CS: U7.4 (CSB), U7.5 (CSB)
/Sensors/PRESSURE_SENSE: R11.2, R12.1
/Sensors/SPI_MISO: U5.5 (SDO), U6.1 (SDO/TA0), U7.6 (SDO), U8.11 (SDO)
/Sensors/SPI_MOSI: U5.16 (SDI), U6.14 (SDA), U7.7 (SDI/SDA), U8.12 (SDI)
/Sensors/SPI_SCK: U5.1 (SCK), U6.13 (SCL), U7.8 (SCLK), U8.10 (SCK)
/Sensors/T_1+: C18.1, C19.1, U8.4 (T+)
/Sensors/T_1-: C19.2, C20.1, U8.2 (BIAS), U8.3 (T-)
/USB_POWER: J101.A4 (VBUS), J101.A9 (VBUS), J101.B4 (VBUS), J101.B9 (VBUS)
GND: C1.2, C2.2, C3.2, C4.1, C5.1, C6.2, C7.2, C8.2, C9.2, C10.2, C11.1, C12.2, C13.2, C14.2, C15.2, C16.2, C17.2, C18.2, C20.2, C21.2, C22.2, C23.2, D1.1 (K), IC1.10 (GND_1), IC1.12 (GND_2), IC1.13 (GND_3), IC1.24 (GND_4), J1.3, J2.2 (Ext), J3.2 (Ext), J101.A1 (GND), J101.A12 (GND), J101.B1 (GND), J101.B12 (GND), R12.2, R112.1, R113.1, SW1.1, U1.9 (GND), U1.17 (EPAD), U2.1 (GND), U3.2 (GND), U3.8 (GND), U3.11 (GND), U3.12 (GND), U3.18 (GND), U4.4 (GND), U5.9 (GND), U5.11 (GND), U6.2 (SDx), U6.3 (SCx), U6.6 (GND), U6.7 (GND), U7.2 (PS), U7.3 (GND), U8.1 (AGND), U8.14 (DGND), U9.3 (GND), U9.7 (EP), U104.3 (GND)
unnamed: C4.2, R3.1, SW1.2
unnamed: D1.2 (A), R13.2
unnamed: J101.A5 (CC1), R112.2
unnamed: J101.B5 (CC2), R113.2
unnamed: R1.1, U1.11 (ADDR)
unnamed: C1.1, R1.2, U1.8 (DECAP)
unnamed: C13.1, U5.10 (CAP)
